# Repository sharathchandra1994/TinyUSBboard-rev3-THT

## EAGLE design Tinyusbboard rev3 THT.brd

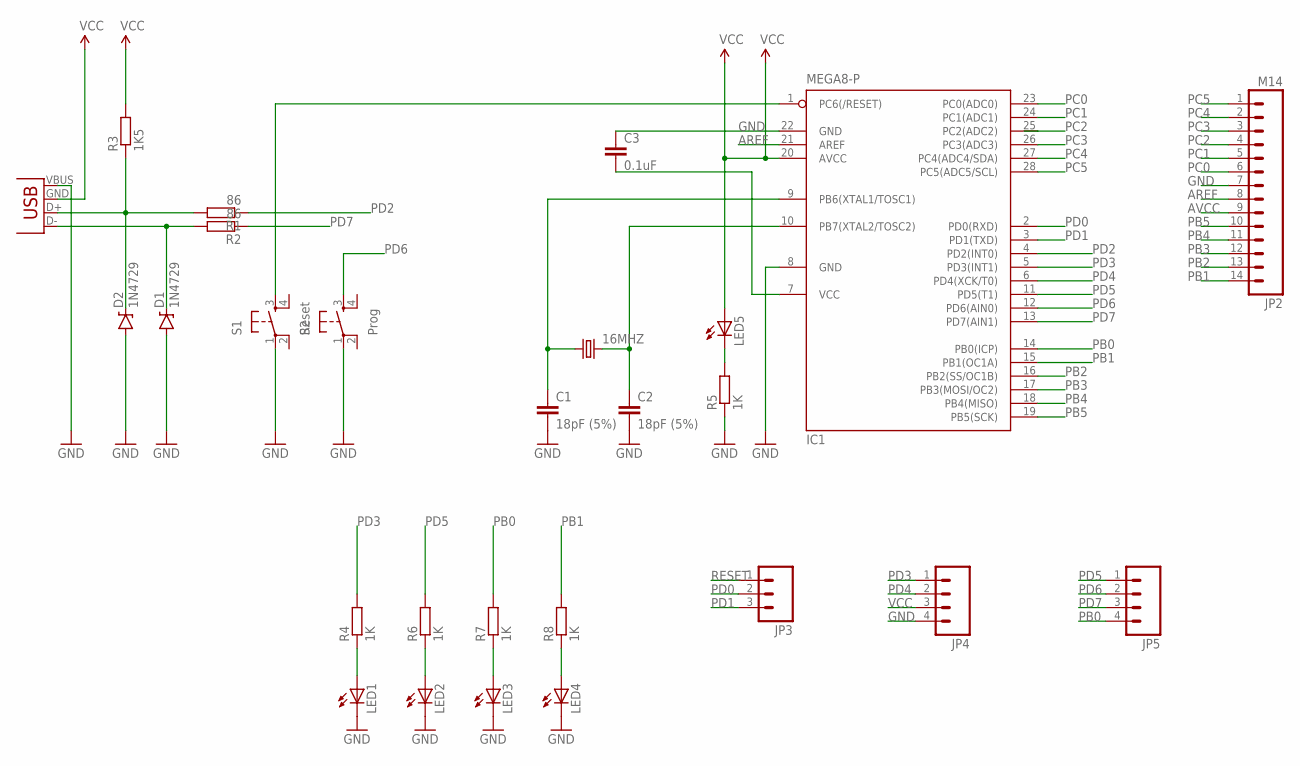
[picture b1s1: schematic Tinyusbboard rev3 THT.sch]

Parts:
16MHZ: CRYSTALTC26V; TC26V
C1, C2: 18pF (5%); C025-024X044
C3: 0.1uF; C025-024X044
D1, D2: 1N4729; DIODE-ZENER
IC1: MEGA8-P; DIL28-3
JP1: USB-A-H
JP2: M14; 1X14
JP3: M03PTH; 1X03
JP4, JP5: M04PTH; 1X04
LED1, LED2, LED3, LED4, LED5: LED3MM
R1, R2: 86; 0204/7
R3: 1K5; 0204/7
R4, R5, R8: 1K; 0204/7
R6, R7: 1K; 0204V
S1: Reset; TACTILE-PTH
S2: Prog; TACTILE-PTH

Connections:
AREF: IC1.21 (AREF), JP2.8
AVCC: JP2.9
D+: D1.P$1 (C), JP1.D- (D+), R2.2
D-: D2.P$1 (C), JP1.D+ (D-), R1.2, R3.1
GND: C1.2, C2.2, C3.1, D1.P$2 (A), D2.P$2 (A), IC1.8 (GND), IC1.22 (GND), JP1.VBUS (GND), JP2.7, JP4.4, LED1.K (C), LED2.K (C), LED3.K (C), LED4.K (C), R5.1, S1.1, S2.1
unnamed: C3.2, IC1.7 (VCC)
unnamed: LED5.K (C), R5.2
unnamed: LED1.A, R4.1
unnamed: LED2.A, R6.1
unnamed: LED3.A, R7.1
unnamed: LED4.A, R8.1
unnamed: 16MHZ.1, C1.1, IC1.9 (PB6(XTAL1/TOSC1))
unnamed: 16MHZ.2, C2.1, IC1.10 (PB7(XTAL2/TOSC2))
PB0: IC1.14 (PB0(ICP)), JP5.4, R7.2
PB1: IC1.15 (PB1(OC1A)), JP2.14, R8.2
PB2: IC1.16 (PB2(SS/OC1B)), JP2.13
PB3: IC1.17 (PB3(MOSI/OC2)), JP2.12
PB4: IC1.18 (PB4(MISO)), JP2.11
PB5: IC1.19 (PB5(SCK)), JP2.10
PC0: IC1.23 (PC0(ADC0)), JP2.6
PC1: IC1.24 (PC1(ADC1)), JP2.5
PC2: IC1.25 (PC2(ADC2)), JP2.4
PC3: IC1.26 (PC3(ADC3)), JP2.3
PC4: IC1.27 (PC4(ADC4/SDA)), JP2.2
PC5: IC1.28 (PC5(ADC5/SCL)), JP2.1
PD0: IC1.2 (PD0(RXD)), JP3.2
PD1: IC1.3 (PD1(TXD)), JP3.3
PD2: IC1.4 (PD2(INT0)), R1.1
PD3: IC1.5 (PD3(INT1)), JP4.1, R4.2
PD4: IC1.6 (PD4(XCK/T0)), JP4.2
PD5: IC1.11 (PD5(T1)), JP5.1, R6.2
PD6: IC1.12 (PD6(AIN0)), JP5.2, S2.3
PD7: IC1.13 (PD7(AIN1)), JP5.3, R2.1
RESET: IC1.1 (PC6(/RESET)), JP3.1, S1.3
VCC: IC1.20 (AVCC), JP1.GND (VBUS), JP4.3, LED5.A, R3.2

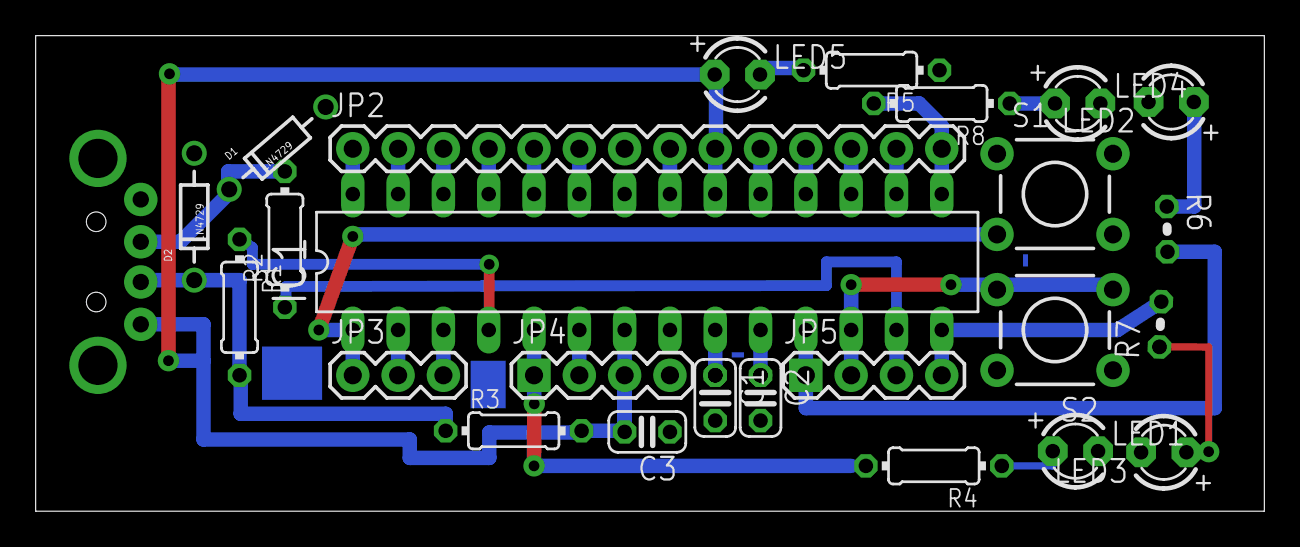
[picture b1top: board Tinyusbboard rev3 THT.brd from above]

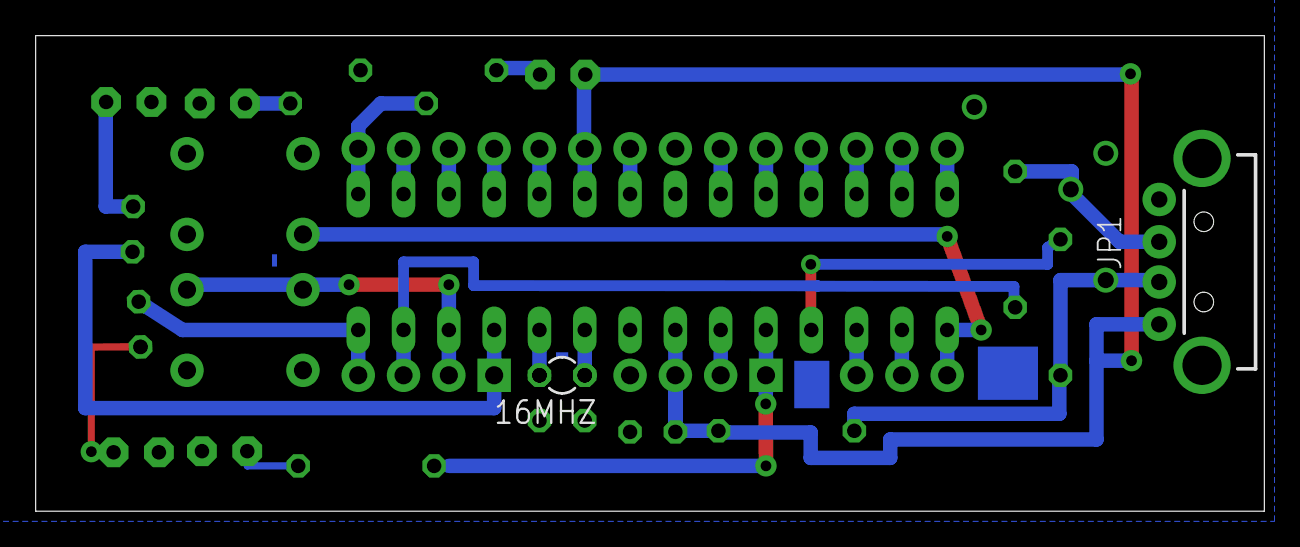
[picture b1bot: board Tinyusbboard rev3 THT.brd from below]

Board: 2 copper layers, 68.9 x 26.7 mm, 27 parts (2 on the bottom side), 34 nets.

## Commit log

2015-01-19 :space_invader: Added .gitattributes & .gitignore files
2015-01-19 TinyUSBboard
    Arduino compatible without extra programmer and/or FTDI chip
    (USB<->serial) needed! Plus exchangeable bootloader!
2015-01-19 test file
2015-01-19 test once again
2015-01-19 remove test.txt

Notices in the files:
parts and their libraries:
SparkFun-Retired: Licensing:Creative Commons ShareAlike 4.0 International - https://creativecommons.org/licenses/by-sa/4.0
